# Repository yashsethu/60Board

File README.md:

# 60Board
A low cost, sleek, and custom 60% keyboard!

I made this program for Hack Club's Hackboard (Hackpad) and Highway programs, but moreso to learn more about PCB design! Also, the ducky I use regularly is starting to get a little old, so this would be the perfect replacement! 

## Schematic

## PCB

## Bill of Materials (BOM)
|    Item    | Quantity | Vendor | Total Price |
| :-------- | :-------: | :----- | ----------: |
| Any MX style keyswitches (I used Gateron Milky Yellow Pros) |  64  |  [Kinetic](https://kineticlabs.com/switches/gateron/gateron-milky-yellow-pro-black-bottom-linear) | $16.10 |
| SSD1306 1.9" OLED | 1  | [Amazon](https://www.google.com/search?q=ssd1306+0.91&oq=ssd1306+0.&gs_lcrp=EgZjaHJvbWUqBggAEEUYOzIGCAAQRRg7MgYIARBFGDkyBggCEEUYQDIICAMQABgWGB4yCAgEEAAYFhgeMggIBRAAGBYYHjIGCAYQRRg8MgYIBxBFGDzSAQgzMDM3ajBqN6gCALACAA&sourceid=chrome&ie=UTF-8) | $6.99 |
| Rotary Encoder (preferably short)    | 1    | [Aliexpress](https://www.aliexpress.us/item/3256804721655912.html?spm=a2g0o.productlist.main.3.3af2EOU3EOU3zl&algo_pvid=58e83ab5-33d5-4674-a6d4-7e8ec393a9a1&algo_exp_id=58e83ab5-33d5-4674-a6d4-7e8ec393a9a1-2&pdp_ext_f=%7B%22order%22%3A%22876%22%2C%22eval%22%3A%221%22%7D&pdp_npi=4%40dis%21USD%212.45%212.45%21%21%2117.46%2117.46%21%40210318c317498592036492270e2eac%2112000035534364746%21sea%21US%216344962744%21X&curPageLogUid=NL2tyjSWWLnT&utparam-url=scene%3Asearch%7Cquery_from%3A) | $1.55 | 
| Keycap set (I liked the Soymilk KOA set) | 1 | [Amazon](https://www.amazon.com/dp/B0DGLBXFHD/ref=twister_B0DHWWLTSR?_encoding=UTF8&th=1) | $26.99 |
| Orpheus Pico (or Raspberry Pi Pico 2) | 1 | [Seeed Studio](https://www.seeedstudio.com/Raspberry-Pi-Pico-2-p-5940.html?srsltid=AfmBOopNDN0RoseM_BDfpGL9q782IZnb89sHLu-LgA_pmGtyh8bIAI12ZJQ&gQT=2) | $4.95 |
| Stabilizer set (Generic Keychron) | 1 | [Keychron](https://www.keychron.com/products/keychron-gold-plated-pcb-mounted-stabilizer-set?page=4&gQT=1) | $8.99 |
| Case (Printed) | 1 | My printer | N/A |
| PCB (JLPCB, PCBWay) | 1 | PCBWay (for me) | $82.57 |

**Total Price:** $148.14

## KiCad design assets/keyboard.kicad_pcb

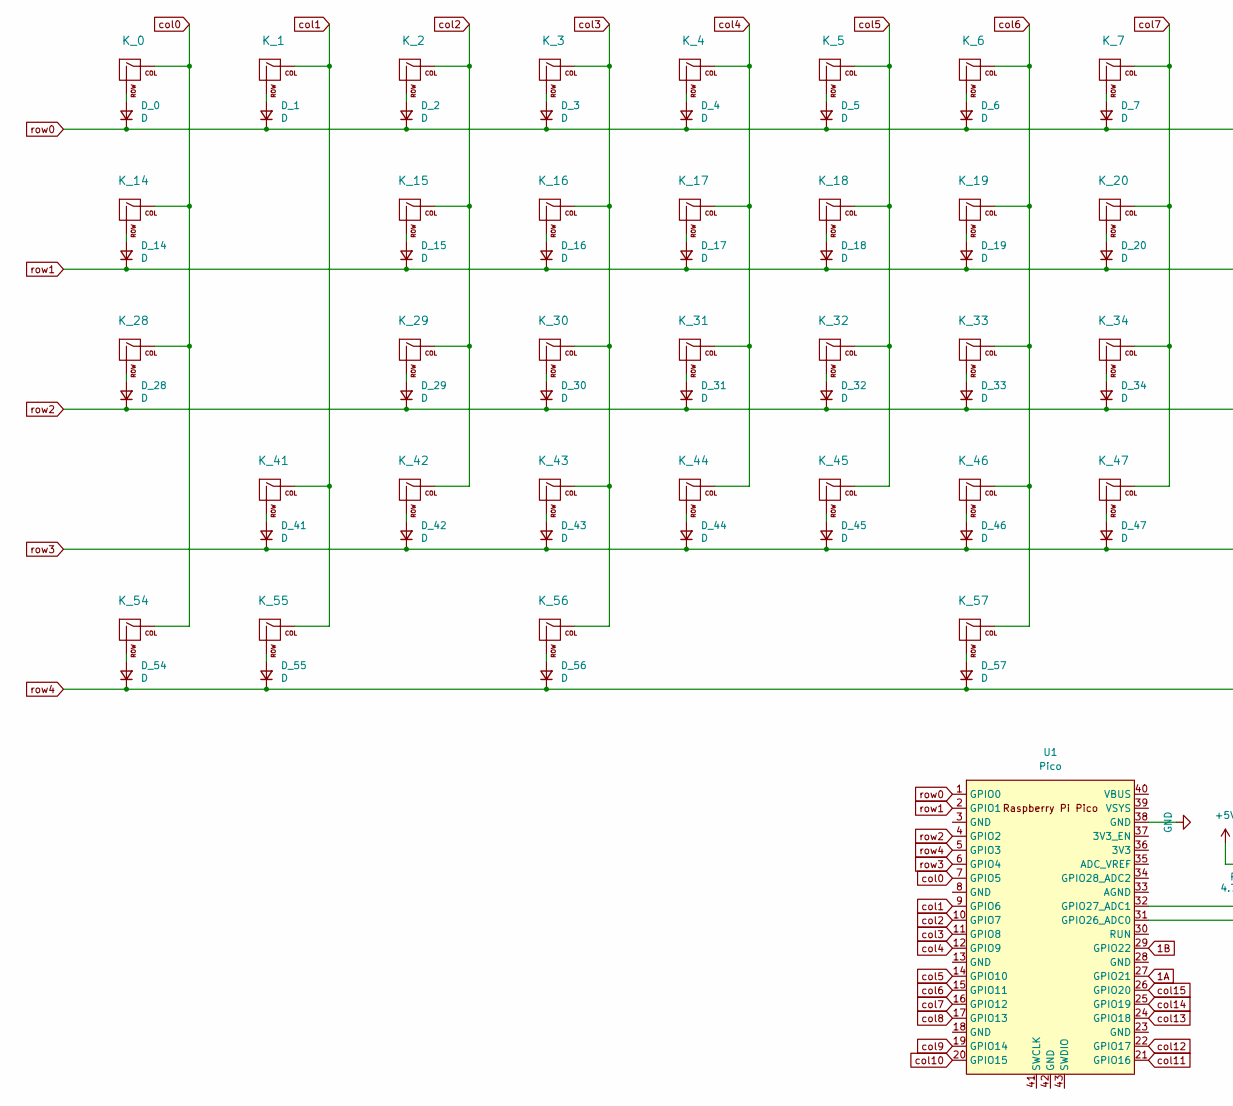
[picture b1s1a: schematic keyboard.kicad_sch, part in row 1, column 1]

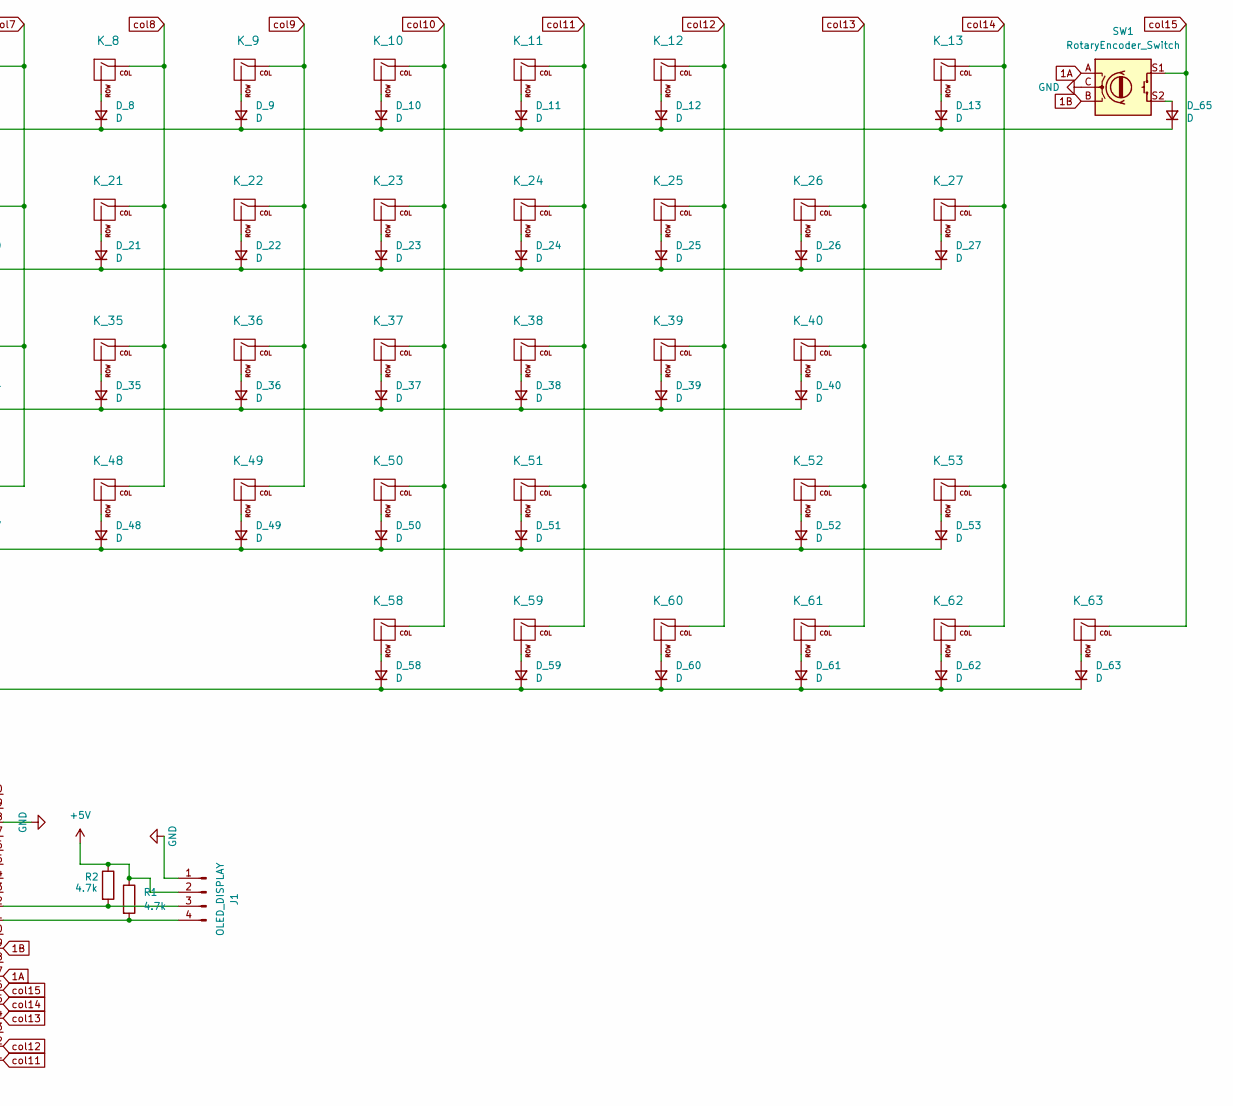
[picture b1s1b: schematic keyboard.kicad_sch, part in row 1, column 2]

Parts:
D_0, D_1, D_2, D_3, D_4, D_5, D_6, D_7, D_8, D_9, D_10, D_11, D_12, D_13, D_14, D_15, D_16, D_17, D_18, D_19, D_20, D_21, D_22, D_23, D_24, D_25, D_26, D_27, D_28, D_29, D_30, D_31, D_32, D_33, D_34, D_35, D_36, D_37, D_38, D_39, D_40, D_41, D_42, D_43, D_44, D_45, D_46, D_47, D_48, D_49, D_50, D_51, D_52, D_53, D_54, D_55, D_56, D_57, D_58, D_59, D_60, D_61, D_62, D_63, D_65: D; D_A-405_P7.62mm_Horizontal
J1: OLED_DISPLAY; 0.91_3D
K_0, K_1, K_2, K_3, K_4, K_5, K_6, K_7, K_8, K_9, K_10, K_11, K_12, K_15, K_16, K_17, K_18, K_19, K_20, K_21, K_22, K_23, K_24, K_25, K_26, K_29, K_30, K_31, K_32, K_33, K_34, K_35, K_36, K_37, K_38, K_39, K_42, K_43, K_44, K_45, K_46, K_47, K_48, K_49, K_50, K_51, K_53, K_58, K_59, K_61, K_62, K_63: KEYSW; SW_Cherry_MX_1.00u_PCB
K_13, K_52: KEYSW; SW_Cherry_MX_2.00u_PCB
K_14, K_27: KEYSW; SW_Cherry_MX_1.50u_PCB
K_28: KEYSW; SW_Cherry_MX_1.75u_PCB
K_40, K_41: KEYSW; SW_Cherry_MX_2.25u_PCB
K_54, K_55, K_56, K_60: KEYSW; SW_Cherry_MX_1.25u_PCB
K_57: KEYSW; SW_Cherry_MX_6.25u_PCB
R1, R2: 4.7k; R_Axial_DIN0204_L3.6mm_D1.6mm_P5.08mm_Horizontal
SW1: RotaryEncoder_Switch; RotaryEncoder_Alps_EC11E-Switch_Vertical_H20mm
U1: Pico; RaspberryPi_Pico_Common_THT

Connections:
1A: SW1.A, U1.27 (GPIO21)
1B: SW1.B, U1.29 (GPIO22)
+5V: J1.2, R1.1, R2.1
GND: J1.1, SW1.C, U1.38 (GND)
unnamed: D_0.2 (A), K_0.2 (ROW)
unnamed: D_1.2 (A), K_1.2 (ROW)
unnamed: D_2.2 (A), K_2.2 (ROW)
unnamed: D_3.2 (A), K_3.2 (ROW)
unnamed: D_4.2 (A), K_4.2 (ROW)
unnamed: D_5.2 (A), K_5.2 (ROW)
unnamed: D_6.2 (A), K_6.2 (ROW)
unnamed: D_7.2 (A), K_7.2 (ROW)
unnamed: D_8.2 (A), K_8.2 (ROW)
unnamed: D_9.2 (A), K_9.2 (ROW)
unnamed: D_10.2 (A), K_10.2 (ROW)
unnamed: D_11.2 (A), K_11.2 (ROW)
unnamed: D_12.2 (A), K_12.2 (ROW)
unnamed: D_13.2 (A), K_13.2 (ROW)
unnamed: D_14.2 (A), K_14.2 (ROW)
unnamed: D_15.2 (A), K_15.2 (ROW)
unnamed: D_16.2 (A), K_16.2 (ROW)
unnamed: D_17.2 (A), K_17.2 (ROW)
unnamed: D_18.2 (A), K_18.2 (ROW)
unnamed: D_19.2 (A), K_19.2 (ROW)
unnamed: D_20.2 (A), K_20.2 (ROW)
unnamed: D_21.2 (A), K_21.2 (ROW)
unnamed: D_22.2 (A), K_22.2 (ROW)
unnamed: D_23.2 (A), K_23.2 (ROW)
unnamed: D_24.2 (A), K_24.2 (ROW)
unnamed: D_25.2 (A), K_25.2 (ROW)
unnamed: D_26.2 (A), K_26.2 (ROW)
unnamed: D_27.2 (A), K_27.2 (ROW)
unnamed: D_28.2 (A), K_28.2 (ROW)
unnamed: D_29.2 (A), K_29.2 (ROW)
unnamed: D_30.2 (A), K_30.2 (ROW)
unnamed: D_31.2 (A), K_31.2 (ROW)
unnamed: D_32.2 (A), K_32.2 (ROW)
unnamed: D_33.2 (A), K_33.2 (ROW)
unnamed: D_34.2 (A), K_34.2 (ROW)
unnamed: D_35.2 (A), K_35.2 (ROW)
unnamed: D_36.2 (A), K_36.2 (ROW)
unnamed: D_37.2 (A), K_37.2 (ROW)
unnamed: D_38.2 (A), K_38.2 (ROW)
unnamed: D_39.2 (A), K_39.2 (ROW)
unnamed: D_40.2 (A), K_40.2 (ROW)
unnamed: D_41.2 (A), K_41.2 (ROW)
unnamed: D_42.2 (A), K_42.2 (ROW)
unnamed: D_43.2 (A), K_43.2 (ROW)
unnamed: D_44.2 (A), K_44.2 (ROW)
unnamed: D_45.2 (A), K_45.2 (ROW)
unnamed: D_46.2 (A), K_46.2 (ROW)
unnamed: D_47.2 (A), K_47.2 (ROW)
unnamed: D_48.2 (A), K_48.2 (ROW)
unnamed: D_49.2 (A), K_49.2 (ROW)
unnamed: D_50.2 (A), K_50.2 (ROW)
unnamed: D_51.2 (A), K_51.2 (ROW)
unnamed: D_52.2 (A), K_52.2 (ROW)
unnamed: D_53.2 (A), K_53.2 (ROW)
unnamed: D_54.2 (A), K_54.2 (ROW)
unnamed: D_55.2 (A), K_55.2 (ROW)
unnamed: D_56.2 (A), K_56.2 (ROW)
unnamed: D_57.2 (A), K_57.2 (ROW)
unnamed: D_58.2 (A), K_58.2 (ROW)
unnamed: D_59.2 (A), K_59.2 (ROW)
unnamed: D_60.2 (A), K_60.2 (ROW)
unnamed: D_61.2 (A), K_61.2 (ROW)
unnamed: D_62.2 (A), K_62.2 (ROW)
unnamed: D_63.2 (A), K_63.2 (ROW)
unnamed: D_65.2 (A), SW1.S2
unnamed: J1.3, R2.2, U1.32 (GPIO27_ADC1)
unnamed: J1.4, R1.2, U1.31 (GPIO26_ADC0)
col0: K_0.1 (COL), K_14.1 (COL), K_28.1 (COL), K_54.1 (COL), U1.7 (GPIO5)
col1: K_1.1 (COL), K_41.1 (COL), K_55.1 (COL), U1.9 (GPIO6)
col2: K_2.1 (COL), K_15.1 (COL), K_29.1 (COL), K_42.1 (COL), U1.10 (GPIO7)
col3: K_3.1 (COL), K_16.1 (COL), K_30.1 (COL), K_43.1 (COL), K_56.1 (COL), U1.11 (GPIO8)
col4: K_4.1 (COL), K_17.1 (COL), K_31.1 (COL), K_44.1 (COL), U1.12 (GPIO9)
col5: K_5.1 (COL), K_18.1 (COL), K_32.1 (COL), K_45.1 (COL), U1.14 (GPIO10)
col6: K_6.1 (COL), K_19.1 (COL), K_33.1 (COL), K_46.1 (COL), K_57.1 (COL), U1.15 (GPIO11)
col7: K_7.1 (COL), K_20.1 (COL), K_34.1 (COL), K_47.1 (COL), U1.16 (GPIO12)
col8: K_8.1 (COL), K_21.1 (COL), K_35.1 (COL), K_48.1 (COL), U1.17 (GPIO13)
col9: K_9.1 (COL), K_22.1 (COL), K_36.1 (COL), K_49.1 (COL), U1.19 (GPIO14)
col10: K_10.1 (COL), K_23.1 (COL), K_37.1 (COL), K_50.1 (COL), K_58.1 (COL), U1.20 (GPIO15)
col11: K_11.1 (COL), K_24.1 (COL), K_38.1 (COL), K_51.1 (COL), K_59.1 (COL), U1.21 (GPIO16)
col12: K_12.1 (COL), K_25.1 (COL), K_39.1 (COL), K_60.1 (COL), U1.22 (GPIO17)
col13: K_26.1 (COL), K_40.1 (COL), K_52.1 (COL), K_61.1 (COL), U1.24 (GPIO18)
col14: K_13.1 (COL), K_27.1 (COL), K_53.1 (COL), K_62.1 (COL), U1.25 (GPIO19)
col15: K_63.1 (COL), SW1.S1, U1.26 (GPIO20)
row0: D_0.1 (K), D_1.1 (K), D_2.1 (K), D_3.1 (K), D_4.1 (K), D_5.1 (K), D_6.1 (K), D_7.1 (K), D_8.1 (K), D_9.1 (K), D_10.1 (K), D_11.1 (K), D_12.1 (K), D_13.1 (K), D_65.1 (K), U1.1 (GPIO0)
row1: D_14.1 (K), D_15.1 (K), D_16.1 (K), D_17.1 (K), D_18.1 (K), D_19.1 (K), D_20.1 (K), D_21.1 (K), D_22.1 (K), D_23.1 (K), D_24.1 (K), D_25.1 (K), D_26.1 (K), D_27.1 (K), U1.2 (GPIO1)
row2: D_28.1 (K), D_29.1 (K), D_30.1 (K), D_31.1 (K), D_32.1 (K), D_33.1 (K), D_34.1 (K), D_35.1 (K), D_36.1 (K), D_37.1 (K), D_38.1 (K), D_39.1 (K), D_40.1 (K), U1.4 (GPIO2)
row3: D_41.1 (K), D_42.1 (K), D_43.1 (K), D_44.1 (K), D_45.1 (K), D_46.1 (K), D_47.1 (K), D_48.1 (K), D_49.1 (K), D_50.1 (K), D_51.1 (K), D_52.1 (K), D_53.1 (K), U1.6 (GPIO4)
row4: D_54.1 (K), D_55.1 (K), D_56.1 (K), D_57.1 (K), D_58.1 (K), D_59.1 (K), D_60.1 (K), D_61.1 (K), D_62.1 (K), D_63.1 (K), U1.5 (GPIO3)

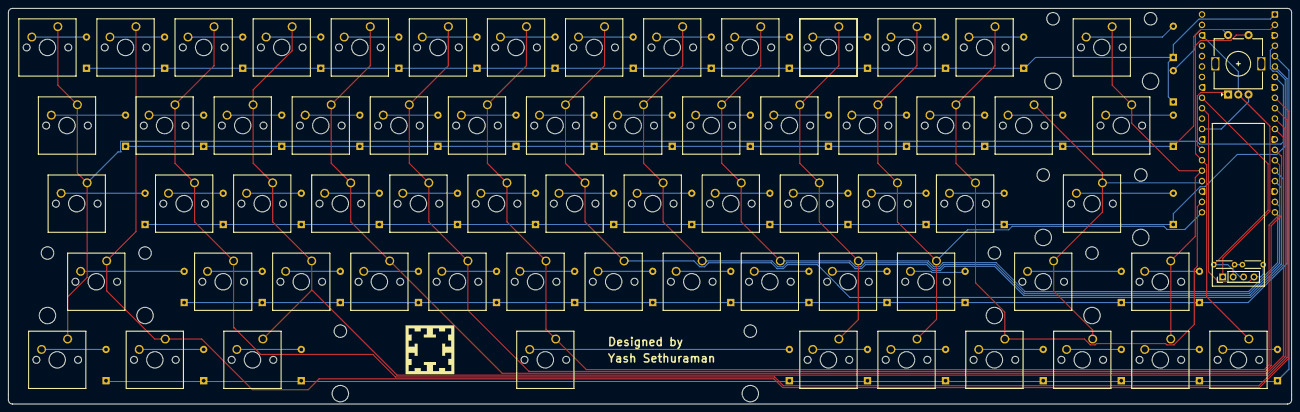
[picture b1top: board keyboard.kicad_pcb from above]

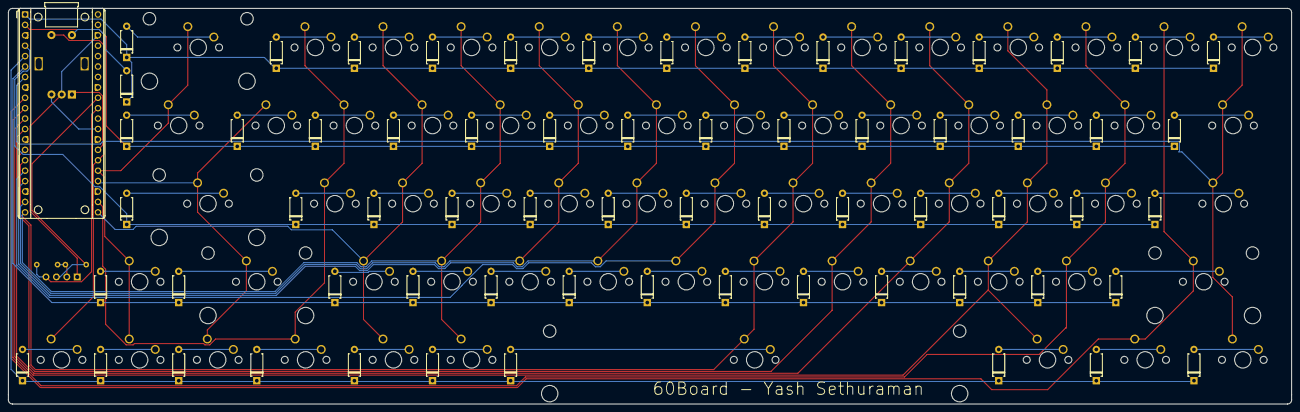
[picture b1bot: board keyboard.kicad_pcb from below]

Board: 2 copper layers, 313.0 x 96.5 mm, 134 parts (66 on the bottom side), 92 nets.

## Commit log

2025-06-07 Add files
2025-06-11 Add firmware
